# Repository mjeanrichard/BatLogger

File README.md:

#BatLogger

An Adruino based BatLogger with evaluation Software.

##Circuit

###PCB (Fritzing)

##Links
* Circuit Help http://forum.allaboutcircuits.com/showthread.php?t=96364
* ArduBat http://home.earthlink.net/~bat-detector/ArduBat/

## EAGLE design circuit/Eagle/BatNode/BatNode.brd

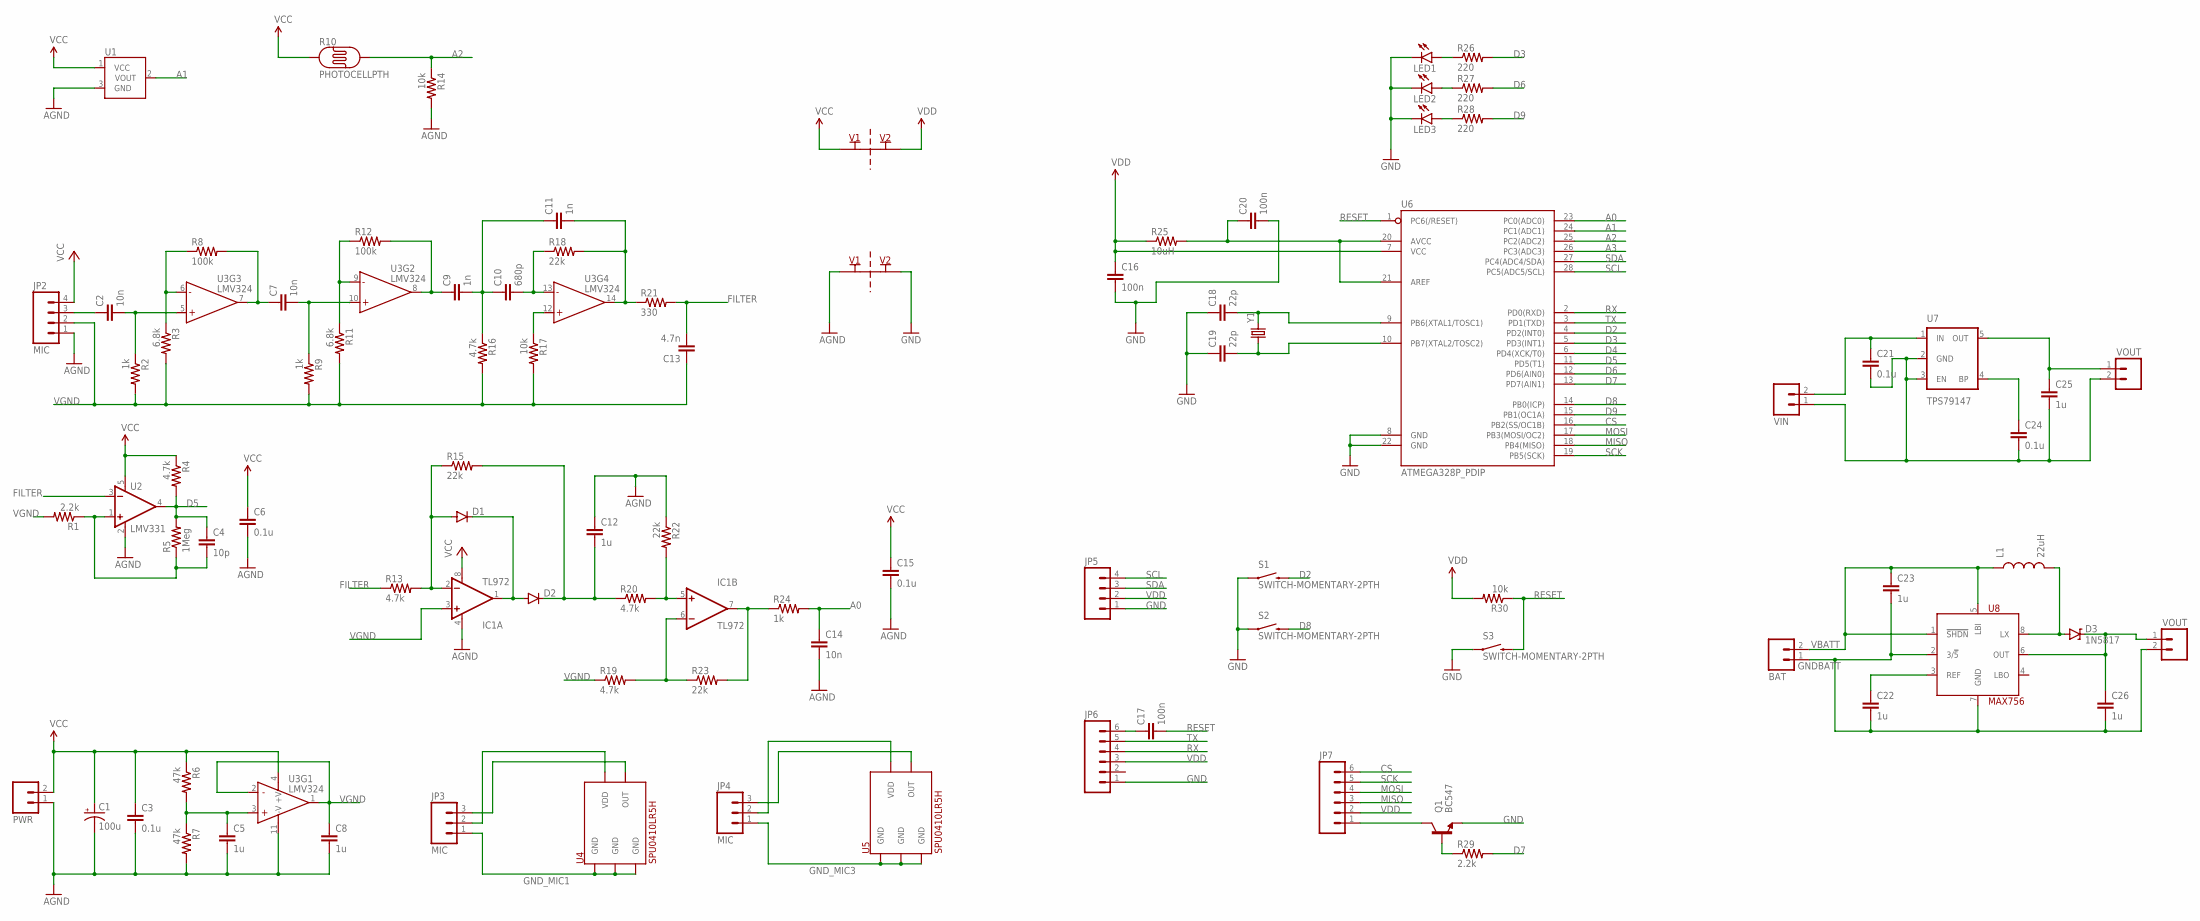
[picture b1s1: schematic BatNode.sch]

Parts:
C1: 100u; CPOL-RADIAL-100UF-25V
C2, C7, C14: 10n; C025-030X050
C3, C6, C15, C21, C24: 0.1u; 0805
C4: 10p; C025-030X050
C5, C8: 1u; 0805
C9, C11: 1n; C025-030X050
C10: 680p; C025-030X050
C12, C22, C23, C25, C26: 1u; C025-030X050
C13: 4.7n; C025-030X050
C16, C17, C20: 100n; 0805
C18, C19: 22p; CAP-PTH-SMALL
D1, D2: DIODE1N4148; DIODE-1N4148
D3: 1N5817; DIODE-ZENER
IC1: TL972; SO08
JP1: PWR; 1X02_LOCK
JP2: MIC; 1X04
JP3, JP4: MIC; 1X03_LOCK
JP5: M04LOCK; 1X04_LOCK
JP6, JP7: M06LOCK; 1X06_LOCK
JP8: BAT; 1X02_LOCK
JP9: VIN; 1X02_LOCK
JP10, JP11: VOUT; 1X02_LOCK
L1: 22uH; C2020
LED1, LED2, LED3: LED5MM
Q1: BC547; TO-92-AMMO
R1, R29: 2.2k; AXIAL-0.3
R2, R9, R24: 1k; AXIAL-0.3
R3, R11: 6.8k; AXIAL-0.3
R4, R13, R16, R19, R20: 4.7k; AXIAL-0.3
R5: 1Meg; AXIAL-0.3
R6, R7: 47k; AXIAL-0.3
R8, R12: 100k; AXIAL-0.3
R10: PHOTOCELLPTH; PHOTOCELL
R14, R17, R30: 10k; AXIAL-0.3
R15, R18, R22, R23: 22k; AXIAL-0.3
R21: 330; AXIAL-0.3
R25: 10uH; AXIAL-0.3
R26, R27, R28: 220; AXIAL-0.3
S1, S2, S3: SWITCH-MOMENTARY-2PTH; TACTILE-PTH
U1: TMP36GT9; TO-92
U2: LMV331; SOT23-5
U3: LMV324; SO014
U4, U5: SPU0410LR5H
U6: ATMEGA328P_PDIP; DIL28-3
U7: TPS79147; SOT23-5
U8: MAX756; SO08
X11, X12: SUPPLY_CONNECT; 2PT_GND_TIE
Y1: CRYSTALHC49UV; HC49U-V

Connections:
A0: C14.1, R24.P$2 (2), U6.23 (PC0(ADC0))
A1: U1.2 (VOUT), U6.24 (PC1(ADC1))
A2: R10.2, R14.P$1 (1), U6.25 (PC2(ADC2))
A3: U6.26 (PC3(ADC3))
AGND: C1.2 (-), C3.2, C5.2, C6.2, C8.2, C12.1, C14.2, C15.2, IC1.4 (V-), JP1.1, JP2.1, R7.P$2 (2), R14.P$2 (2), R22.P$1 (1), U1.3 (GND), U2.2 (V-), U3.11 (-V), X12.P$1
CS: JP7.6, U6.16 (PB2(SS/OC1B))
D2: S1.3 (2), U6.4 (PD2(INT0))
D3: R26.P$2 (2), U6.5 (PD3(INT1))
D4: U6.6 (PD4(XCK/T0))
D5: C4.1, R4.P$2 (2), R5.P$2 (2), U2.4 (OUT), U6.11 (PD5(T1))
D6: R27.P$2 (2), U6.12 (PD6(AIN0))
D7: R29.P$2 (2), U6.13 (PD7(AIN1))
D8: S2.3 (2), U6.14 (PB0(ICP))
D9: R28.P$2 (2), U6.15 (PB1(OC1A))
FILTER: C13.2, R13.P$1 (1), R21.P$2 (2), U2.3 (-IN)
GND: C16.2, C18.1, C19.1, C20.2, JP5.1, JP6.1, LED1.K (C), LED2.K (C), LED3.K (C), Q1.3 (E), S1.1, S2.1, S3.1, U6.8 (GND), U6.22 (GND), X12.P$2
GNDBATT: C22.2, C23.2, C26.2, JP8.1, JP11.2, U8.2 (3/!5), U8.7 (GND)
GNDIN: C21.2, C24.2, C25.2, JP9.1, JP10.2, U7.2 (GND), U7.3 (EN)
GND_MIC1: JP3.1, U4.2 (GND), U4.3 (GND), U4.5 (GND)
GND_MIC3: JP4.1, U5.2 (GND), U5.3 (GND), U5.5 (GND)
MISO: JP7.3, U6.18 (PB4(MISO))
MOSI: JP7.4, U6.17 (PB3(MOSI/OC2))
unnamed: C5.1, R6.P$2 (2), R7.P$1 (1), U3.3 (+IN)
unnamed: C2.2, R2.P$1 (1), U3.5 (+IN)
unnamed: R3.P$1 (1), R8.P$1 (1), U3.6 (-IN)
unnamed: C7.1, R8.P$2 (2), U3.7 (OUT)
unnamed: C7.2, R9.P$1 (1), U3.10 (+IN)
unnamed: C9.1, R12.P$2 (2), U3.8 (OUT)
unnamed: R11.P$1 (1), R12.P$1 (1), U3.9 (-IN)
unnamed: C9.2, C10.1, C11.1, R16.P$1 (1)
unnamed: R17.P$1 (1), U3.12 (+IN)
unnamed: C10.2, R18.P$1 (1), U3.13 (-IN)
unnamed: C2.1, JP2.3
unnamed: C4.2, R1.P$1 (1), R5.P$1 (1), U2.1 (+IN)
unnamed: C17.1, JP6.6
unnamed: JP3.2, U4.4 (VDD)
unnamed: JP3.3, U4.1 (OUT)
unnamed: C18.2, U6.9 (PB6(XTAL1/TOSC1)), Y1.2
unnamed: C19.2, U6.10 (PB7(XTAL2/TOSC2)), Y1.1
unnamed: JP7.1, Q1.1 (C)
unnamed: C20.1, R25.P$2 (2), U6.20 (AVCC), U6.21 (AREF)
unnamed: JP4.2, U5.4 (VDD)
unnamed: Q1.2 (B), R29.P$1 (1)
unnamed: LED1.A, R26.P$1 (1)
unnamed: LED2.A, R27.P$1 (1)
unnamed: LED3.A, R28.P$1 (1)
unnamed: D3.P$2 (A), L1.P$2 (2), U8.8 (LX)
unnamed: C24.1, U7.4 (BP)
unnamed: D1.A, IC1.2 (-IN), R13.P$2 (2), R15.P$1 (1)
unnamed: JP4.3, U5.1 (OUT)
unnamed: D1.C, D2.A, IC1.1 (OUT)
unnamed: IC1.5 (+IN), R20.P$2 (2), R22.P$2 (2)
unnamed: C12.2, D2.C, R15.P$2 (2), R20.P$1 (1)
unnamed: IC1.6 (-IN), R19.P$2 (2), R23.P$1 (1)
unnamed: C26.1, D3.P$1 (C), JP11.1, U8.6 (OUT)
unnamed: C22.1, U8.3 (REF)
RESET: C17.2, R30.P$1 (1), S3.3 (2), U6.1 (PC6(/RESET))
RX: JP6.4, U6.2 (PD0(RXD))
SCK: JP7.5, U6.19 (PB5(SCK))
SCL: JP5.4, U6.28 (PC5(ADC5/SCL))
SDA: JP5.3, U6.27 (PC4(ADC4/SDA))
TX: JP6.5, U6.3 (PD1(TXD))
VBATT: C23.1, JP8.2, L1.P$1 (1), U8.1 (!SHDN), U8.5 (LBI)
VCC: C1.1 (+), C3.1, C6.1, C15.1, IC1.8 (V+), JP1.2, JP2.4, R4.P$1 (1), R6.P$1 (1), R10.1, U1.1 (VCC), U2.5 (V+), U3.4 (+V), X11.P$1
VDD: C16.1, JP5.2, JP6.3, JP7.2, R25.P$1 (1), R30.P$2 (2), U6.7 (VCC), X11.P$2
VGND: C8.1, C13.1, IC1.3 (+IN), JP2.2, R1.P$2 (2), R2.P$2 (2), R3.P$2 (2), R9.P$2 (2), R11.P$2 (2), R16.P$2 (2), R17.P$2 (2), R19.P$1 (1), U3.1 (OUT), U3.2 (-IN)
VIN: C21.1, JP9.2, U7.1 (IN)
VOUT: C25.1, JP10.1, U7.5 (OUT)
X1: IC1.7 (OUT), R23.P$2 (2), R24.P$1 (1)
XXX: C11.2, R18.P$2 (2), R21.P$1 (1), U3.14 (OUT)

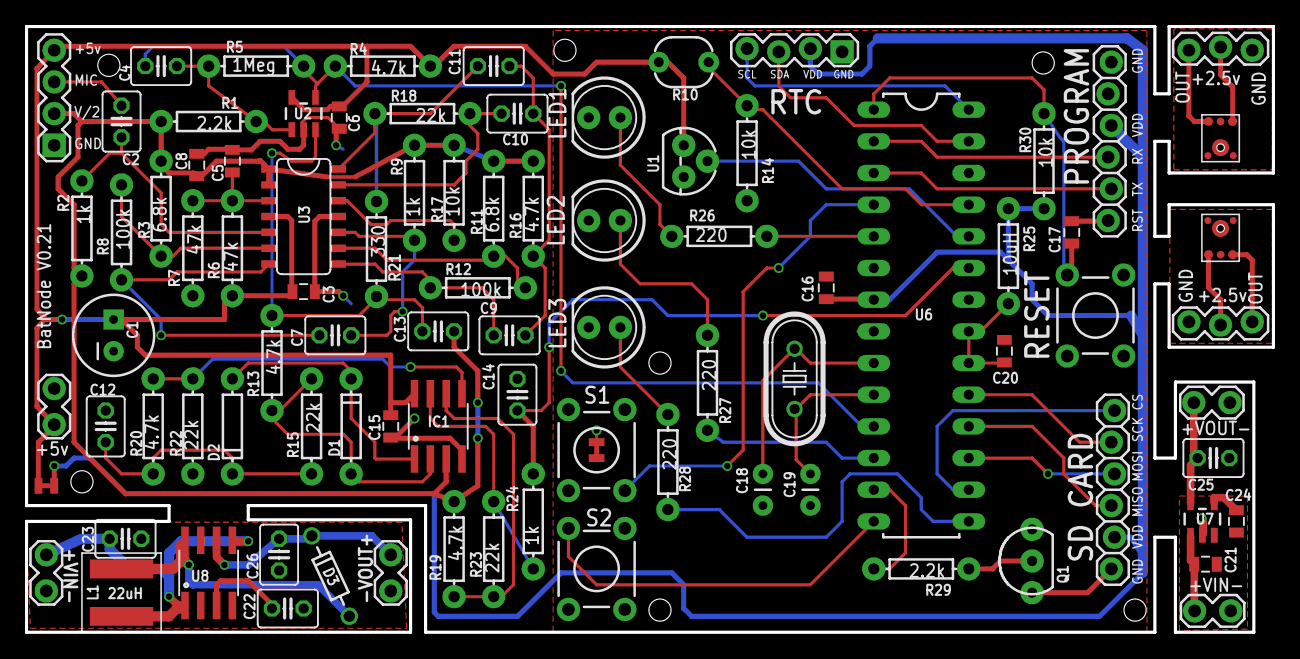
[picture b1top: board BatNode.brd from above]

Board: 2 copper layers, 100.0 x 48.6 mm, 90 parts (0 on the bottom side), 68 nets.

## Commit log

2014-04-20 Initial Checkin.
2014-04-21 Updated Documentation
2014-04-21 Reworked Models
2014-05-29 BatLogger V0.2 PCB
2014-05-29 BatLogger V0.2 PCB (RTC Connector turned)
2014-05-29 Arduino Skript an neue SDFat Library angepasst.
2014-06-16 BatLogger und Setup Solution hinzugefügt.
2014-06-16 Kleine Korrekturen am PCB
2014-06-16 BatLogger App erweitert.
2014-07-20 Simulationen für unterschiedliche Varianten
2014-08-03 BatLogger auf Basis von Timer1
2014-08-05 PCB V0.3 (LM386)
2014-08-08 PCB V0.3.1 (LM386)
2014-10-28 Simple Indicator hinzugefügt.
2015-01-25 Arduino-Code Archive
2015-01-25 BatNode v0.2
2015-03-26 BatNode v0.21

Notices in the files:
parts and their libraries:
SparkFun-Capacitors: Licensing: Creative Commons ShareAlike 4.0 International - https://creativecommons.org/licenses/by-sa/4.0
